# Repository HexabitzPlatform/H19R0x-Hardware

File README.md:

# H19R0x-Hardware
Hexabitz 38 V/10A Sensored BLDC Module Hardware Design

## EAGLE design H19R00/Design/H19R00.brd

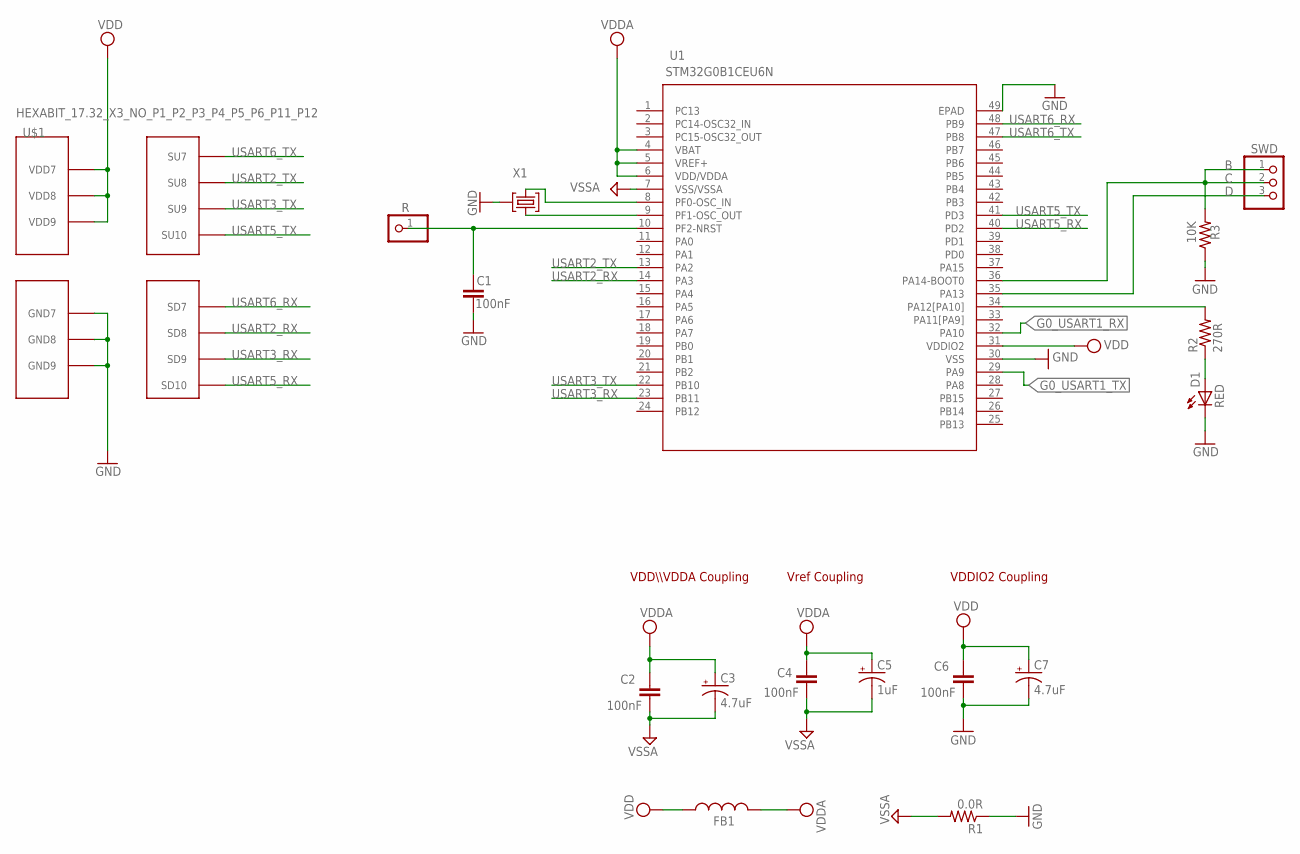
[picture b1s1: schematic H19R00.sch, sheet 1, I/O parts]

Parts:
C1: 100nF; C-0603; TOLERANCE 10%; VOLTAGE_RATING 16.0 V; MPN 0603YC104K4T2A
C2, C4, C6: 100nF; C-0603; TOLERANCE 10%; VOLTAGE_RATING 16.0 V; MPN '0603YC104K4T2A
C3: 4.7uF; C-0805-POL; TOLERANCE 20%; VOLTAGE_RATING 10.0 V; MPN '10TPU4R7MSI
C5: 1uF; C-0805-POL; TOLERANCE 20%; VOLTAGE_RATING 10.0 V; MPN 'CC0805KKX7R7BB105
C7: 4.7uF; C-0805-POL; TOLERANCE 10%; VOLTAGE_RATING 16.0 V; MPN '10TPU4R7MSI
D1: RED; VLMS1300-GS08
FB1: FB-TDK_MMZ1608Y300B; MPN MMZ1608Y300BTA00
R: PINHD-1X1; 1X01
R1: 0.0R; R-0603; MPN RC0603JR-070RL
R2: 270R; R-0603; MPN 'ERJ-3GEYJ271V
R3: 10K; R-0603; MPN '060300J0103T5E
SWD: PINHD-1X3; 1X03
U1: STM32G0B1CEU6N; HEXABITZ_ICS_QFN_B1CEU6_STM-L
U$1: HEXABIT_17.32_X3_NO_P1_P2_P3_P4_P5_P6_P11_P12
X1: 8MHZ; XTALL_CSTCE8M00G52; MPN CSTNE8M00G550000R0

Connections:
C: R3.2, SWD.1, SWD.2, U1.36 (PA14-BOOT0)
D: SWD.3, U1.35 (PA13)
G0_USART1_RX: U1.32 (PA10); also elsewhere on the board
G0_USART1_TX: U1.29 (PA9); also elsewhere on the board
GND: C1.1, C6.1, C7.2 (-), D1.C, R1.1, R3.1, U1.30 (VSS), U1.49 (EPAD), U$1.PAD_PD12 (GND7), U$1.PAD_PD17 (GND8), U$1.PAD_PD19 (GND9), X1.P$2 (2)
GND1: C2.1, C3.2 (-), C4.1, C5.2 (-), R1.2, U1.7 (VSS/VSSA); also elsewhere on the board
unnamed: U1.8 (PF0-OSC_IN), X1.P$1 (1)
unnamed: U1.9 (PF1-OSC_OUT), X1.P$3 (3)
unnamed: R2.2, U1.34 (PA12[PA10])
unnamed: D1.A, R2.1
unnamed: C1.2, R.1, U1.10 (PF2-NRST)
USART2_RX: U1.14 (PA3), U$1.PAD_PD1 (SD8)
USART2_TX: U1.13 (PA2), U$1.PAD_PU1 (SU8)
USART3_RX: U1.23 (PB11), U$1.PAD_PD2 (SD9)
USART3_TX: U1.22 (PB10), U$1.PAD_PU2 (SU9)
USART5_RX: U1.40 (PD2), U$1.PAD_PD8 (SD10)
USART5_TX: U1.41 (PD3), U$1.PAD_PU8 (SU10)
USART6_RX: U1.48 (PB9), U$1.PAD_PD3 (SD7)
USART6_TX: U1.47 (PB8), U$1.PAD_PU3 (SU7)
VDD: C6.2, C7.1 (+), FB1.1, U1.31 (VDDIO2), U$1.PAD_PU12 (VDD7), U$1.PAD_PU17 (VDD8), U$1.PAD_PU19 (VDD9); also elsewhere on the board
VDDA: C2.2, C3.1 (+), C4.2, C5.1 (+), FB1.2, U1.4 (VBAT), U1.5 (VREF+), U1.6 (VDD/VDDA)

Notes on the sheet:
VDDIO2 Coupling
VDD\\\VDDA Coupling
Vref Coupling

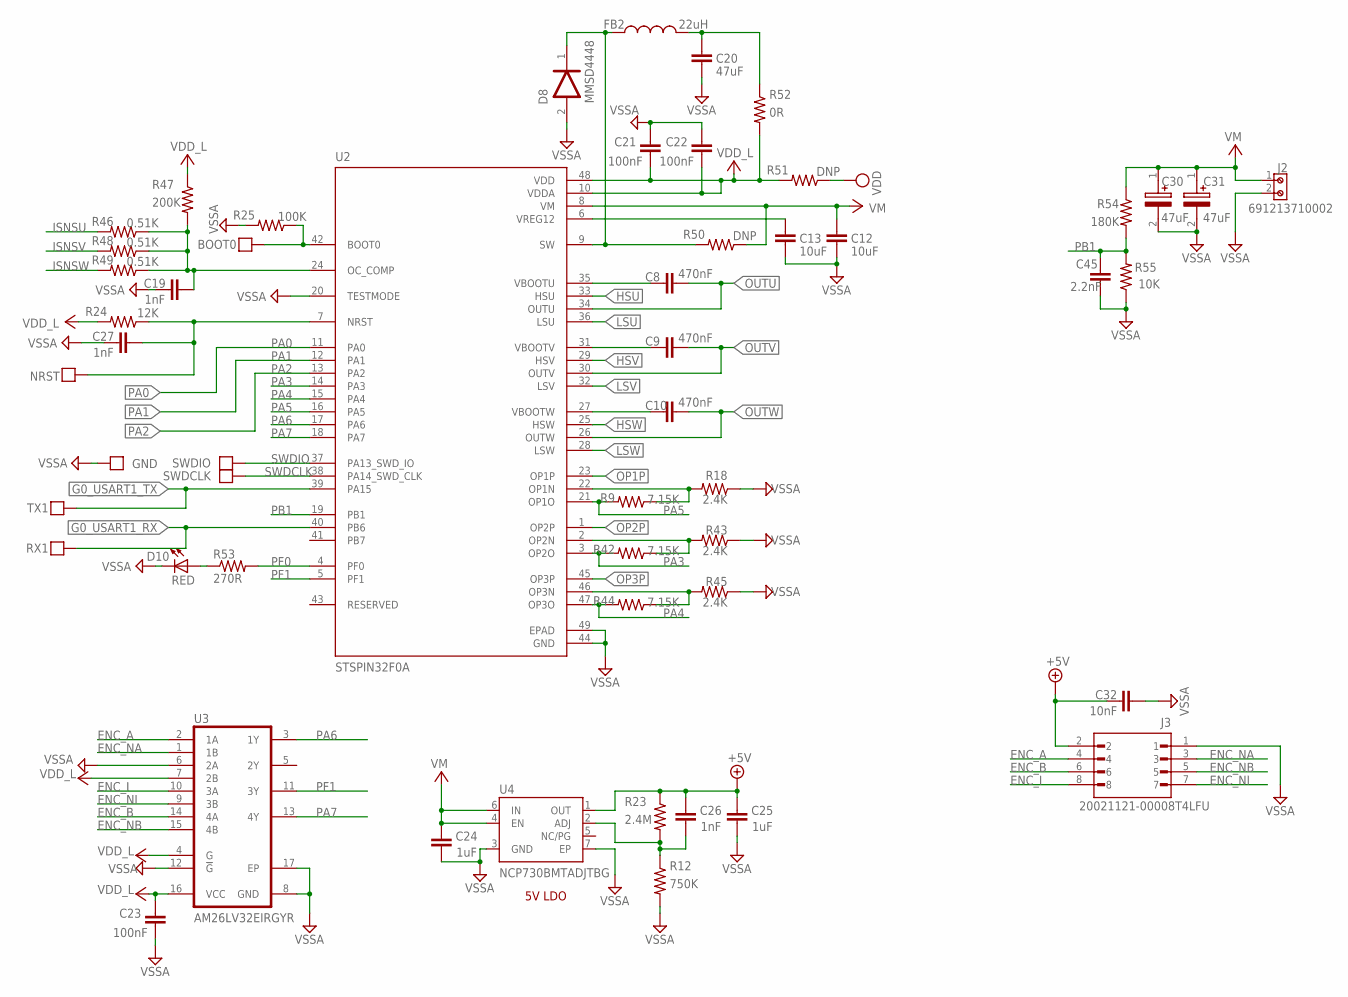
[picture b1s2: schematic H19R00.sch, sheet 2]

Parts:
BOOT0: PAD4
C8, C9, C10: 470nF; C-0603; TOLERANCE 10%; VOLTAGE_RATING 50V; MPN C1608X5R1H474K080AB
C12, C13: 10uF; C-0805; TOLERANCE 10%; VOLTAGE_RATING 50V; MPN GRM21BR61H106KE43K
C19, C26, C27: 1nF; C-0603; TOLERANCE 10%; VOLTAGE_RATING 50V; MPN CC0603KRNPO9BN102
C20: 47uF; C-0805; TOLERANCE 20%; VOLTAGE_RATING 10V; MPN GRM21BR61A476ME15K
C21, C22, C23: 100nF; C-0603; TOLERANCE 10%; VOLTAGE_RATING 16.0 V; MPN '0603YC104K4T2A
C24, C25: 1uF; C-0603; TOLERANCE 10%; VOLTAGE_RATING 50V; MPN UMK107BJ105KA-T
C30, C31: 47uF; CAPPRD350W60D825H1300
C32: 10nF; C-0603; TOLERANCE 10%; VOLTAGE_RATING 100V; MPN C0603X103K1RAC3316
C45: 2.2nF; C-0603; TOLERANCE 10%; VOLTAGE_RATING 16V; MPN C0603C222K4RECAUTO
D8: MMSD4448ONSEMI_MMSD4448_0_0; ONSEMI_MMSD4448_0
D10: RED; VLMS1300-GS08
FB2: 22uH; FB-0805; MPN MLZ2012P220WT000
GND: PAD4
J2: 691213710002
J3: 20021121-00008T4LFU; AMPHENOL_20021121-00008T4LF
NRST: PAD4
R9, R42, R44: 7.15K; R-0603; TOLERANCE 1%; MPN RC0603FR-0710K5L
R12: 750K; R-0603; TOLERANCE 1%; MPN RC0603FR-07750KL
R18, R43, R45: 2.4K; R-0603; TOLERANCE 1%; MPN RC0603FR-132K4L
R23: 2.4M; R-0603; TOLERANCE 1%; MPN RC0603FR-072M4L
R24: 12K; R-0603; TOLERANCE 1%; MPN RC0603FR-0712KL
R25: 100K; R-0603; TOLERANCE 1%; MPN RC0603FR-07100KL
R46, R48, R49: 0.51K; R-0603; TOLERANCE 1%; MPN RC0603FR-102K2L
R47: 200K; R-0603; TOLERANCE 1%; MPN RC0603FR-0718KL
R50, R51: DNP; R-0603; MPN DNP
R52: 0R; R-0603; TOLERANCE 1%; MPN RC0603FR-070RL
R53: 270R; R-0603; MPN 'ERJ-3GEYJ271V
R54: 180K; R-0603; TOLERANCE 1%; MPN RC0603FR-07180KL
R55: 10K; R-0603; MPN '060300J0103T5E
RX1: PAD4
SWDCLK: PAD4
SWDIO: PAD4
TX1: PAD4
U2: STSPIN32F0A; IC_STSPIN32F0A
U3: AM26LV32EIRGYRTEXAS_INSTRUMENTS_AM26LV32EIRGYR_0_0; TEXAS_INSTRUMENTS_AM26LV32EIRGYR_0
U4: NCP730BMTADJTBGON_SEMI_NCP730BMTADJTBG_0_0; ON_SEMI_NCP730BMTADJTBG_0

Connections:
+5V: C25.2, C26.2, C32.1, J3.2, R23.1, U4.1 (OUT); also elsewhere on the board
ENC_A: J3.4, U3.2 (1A)
ENC_B: J3.6, U3.14 (4A)
ENC_I: J3.8, U3.10 (3A)
ENC_NA: J3.3, U3.1 (1B)
ENC_NB: J3.5, U3.15 (4B)
ENC_NI: J3.7, U3.9 (3B)
G0_USART1_RX: RX1.P$1, U2.40 (PB6); also elsewhere on the board
G0_USART1_TX: TX1.P$1, U2.39 (PA15); also elsewhere on the board
GND1: C12.2, C13.2, C19.1, C20.2, C21.2, C22.2, C23.1, C24.1, C25.1, C27.1, C30.2 (-), C31.2 (-), C32.2, C45.1, D8.2 (ANODE), D10.C, GND.P$1, J2.2, J3.1, R12.2, R18.1, R25.2, R43.1, R45.1, R55.1, U2.20 (TESTMODE), U2.44 (GND), U2.49 (EPAD), U3.8 (GND), U3.12 (!G!), U3.17 (EP), U4.3 (GND), U4.7 (EP); also elsewhere on the board
HSU: U2.33 (HSU); also elsewhere on the board
HSV: U2.29 (HSV); also elsewhere on the board
HSW: U2.25 (HSW); also elsewhere on the board
ISNSU: R46.2; also elsewhere on the board
ISNSV: R48.2; also elsewhere on the board
ISNSW: R49.2; also elsewhere on the board
LSU: U2.36 (LSU); also elsewhere on the board
LSV: U2.32 (LSV); also elsewhere on the board
LSW: U2.28 (LSW); also elsewhere on the board
unnamed: R42.1, R43.2, U2.2 (OP2N)
unnamed: C8.2, U2.35 (VBOOTU)
unnamed: C9.2, U2.31 (VBOOTV)
unnamed: C10.2, U2.27 (VBOOTW)
unnamed: C26.1, R12.1, R23.2, U4.2 (ADJ)
unnamed: C27.2, NRST.P$1, R24.1, U2.7 (NRST)
unnamed: C13.1, U2.6 (VREG12)
unnamed: BOOT0.P$1, R25.1, U2.42 (BOOT0)
unnamed: R9.1, R18.2, U2.22 (OP1N)
unnamed: R44.1, R45.2, U2.46 (OP3N)
unnamed: C19.2, R46.1, R47.2, R48.1, R49.1, U2.24 (OC_COMP)
unnamed: D10.A, R53.1
unnamed: D8.1 (CATHODE), FB2.1, R50.2, U2.9 (SW)
unnamed: C20.1, FB2.2, R52.1
OP1P: U2.23 (OP1P); also elsewhere on the board
OP2P: U2.1 (OP2P); also elsewhere on the board
OP3P: U2.45 (OP3P); also elsewhere on the board
OUTU: C8.1, U2.34 (OUTU); also elsewhere on the board
OUTV: C9.1, U2.30 (OUTV); also elsewhere on the board
OUTW: C10.1, U2.26 (OUTW); also elsewhere on the board
PA0: U2.11 (PA0); also elsewhere on the board
PA1: U2.12 (PA1); also elsewhere on the board
PA2: U2.13 (PA2); also elsewhere on the board
PA3: R42.2, U2.3 (OP2O), U2.14 (PA3)
PA4: R44.2, U2.15 (PA4), U2.47 (OP3O)
PA5: R9.2, U2.16 (PA5), U2.21 (OP1O)
PA6: U2.17 (PA6), U3.3 (1Y)
PA7: U2.18 (PA7), U3.13 (4Y)
PB1: C45.2, R54.2, R55.2, U2.19 (PB1)
PF0: R53.2, U2.4 (PF0)
PF1: U2.5 (PF1), U3.11 (3Y)
SWDCLK: SWDCLK.P$1, U2.38 (PA14_SWD_CLK)
SWDIO: SWDIO.P$1, U2.37 (PA13_SWD_IO)
VDD: R51.1; also elsewhere on the board
VDD_L: C21.1, C22.1, C23.2, R24.2, R47.1, R51.2, R52.2, U2.10 (VDDA), U2.48 (VDD), U3.4 (G), U3.7 (2B), U3.16 (VCC); also elsewhere on the board
VM: C12.1, C24.2, C30.1 (+), C31.1 (+), J2.1, R50.1, R54.1, U2.8 (VM), U4.4 (EN), U4.6 (IN); also elsewhere on the board

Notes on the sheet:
5V LDO

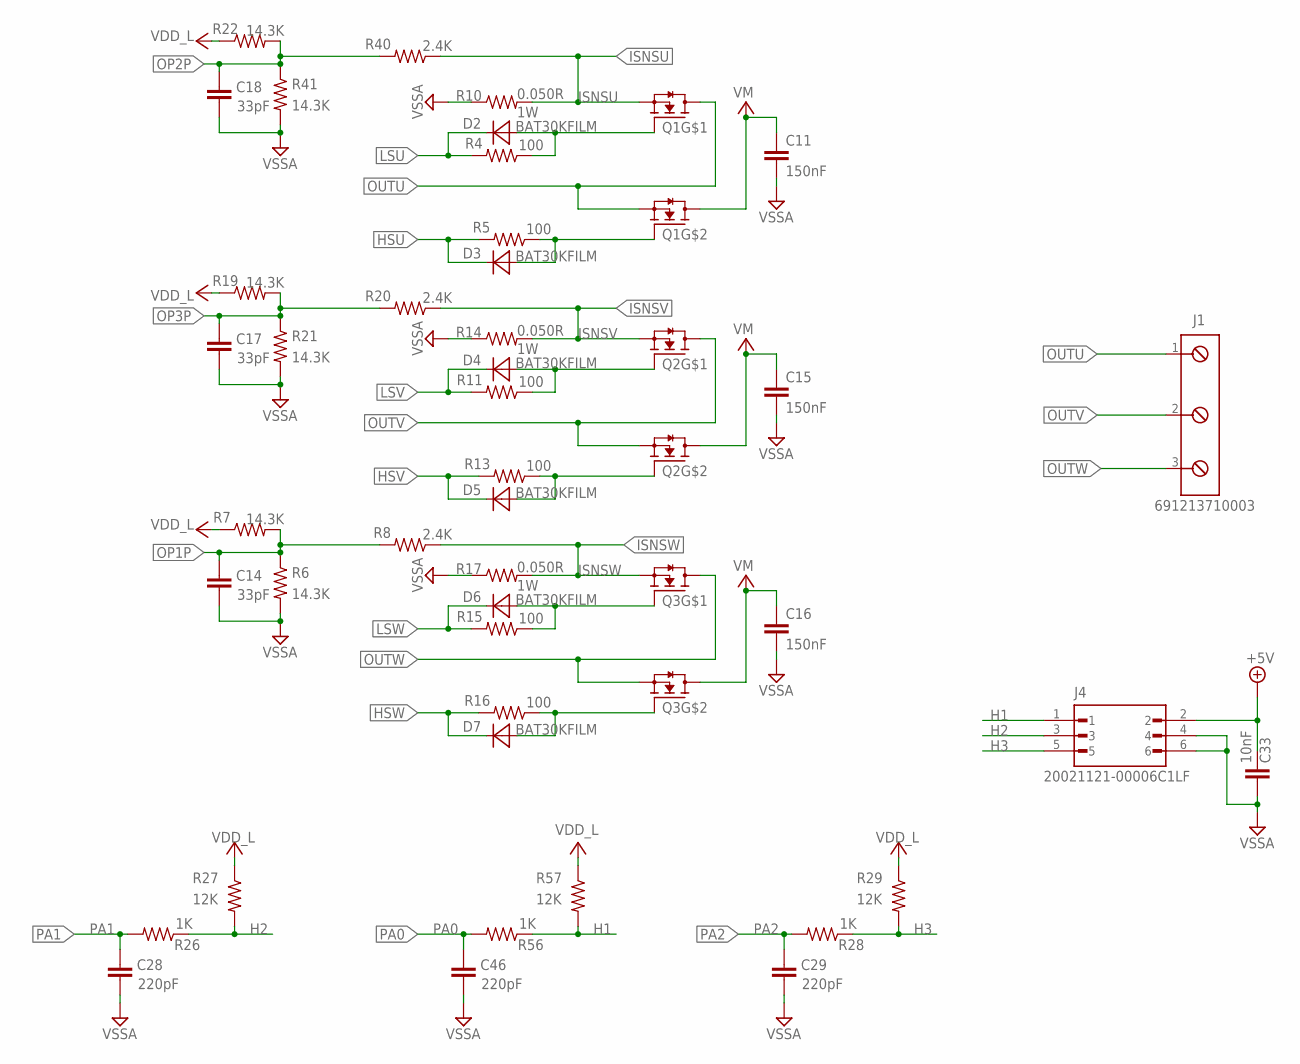
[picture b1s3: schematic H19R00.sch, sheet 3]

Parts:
C11, C15, C16: 150nF; C-0805; TOLERANCE 10%; VOLTAGE_RATING 100V; MPN C0805C154K1REC7800
C14, C17, C18: 33pF; C-0603; TOLERANCE 10%; VOLTAGE_RATING 50V; MPN 0603N330J500CT
C28, C29, C46: 220pF; C-0603; TOLERANCE 10%; VOLTAGE_RATING 50V; MPN 0603B221K500CT
C33: 10nF; C-0603; TOLERANCE 10%; VOLTAGE_RATING 100V; MPN C0603X103K1RAC3316
D2, D3, D4, D5, D6, D7: BAT30KFILM; STMICROELECTRONICS_BAT30KFILM_0
J1: 691213710003
J4: 20021121-00006C1LF; AMPHENOL_20021121-00006C1LF
Q1, Q2, Q3: PJQ5866A_R2_00001; PJQ5866A_R2_00001-8-POWERTDFN
R4, R5, R11, R13, R15, R16: 100; R-0603; TOLERANCE 1%; MPN AC0603FR-13100RL
R6, R7, R19, R21, R22, R41: 14.3K; R-0603; TOLERANCE 1%; MPN RC0603FR-0721KL
R8, R20, R40: 2.4K; R-0603; TOLERANCE 1%; MPN RC0603FR-132K4L
R10, R14, R17: 0.050R; R1206; TOLERANCE 1%; MPN ERJ-8BWFR100V
R26, R28, R56: 1K; R-0603; TOLERANCE 1%; MPN AC0603FR-131KL
R27, R29, R57: 12K; R-0603; TOLERANCE 1%; MPN RC0603FR-0712KL

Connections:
+5V: C33.1, J4.2; also elsewhere on the board
GND1: C11.2, C14.1, C15.2, C16.2, C17.1, C18.1, C28.1, C29.1, C33.2, C46.1, J4.4, J4.6, R6.2, R10.1, R14.1, R17.1, R21.2, R41.2; also elsewhere on the board
H1: J4.1, R56.1, R57.2
H2: J4.3, R26.1, R27.2
H3: J4.5, R28.1, R29.2
HSU: D3.C, R5.2; also elsewhere on the board
HSV: D5.C, R13.2; also elsewhere on the board
HSW: D7.C, R16.2; also elsewhere on the board
ISNSU: Q1.1 (S1), R10.2, R40.1; also elsewhere on the board
ISNSV: Q2.1 (S1), R14.2, R20.1; also elsewhere on the board
ISNSW: Q3.1 (S1), R8.1, R17.2; also elsewhere on the board
LSU: D2.C, R4.2; also elsewhere on the board
LSV: D4.C, R11.2; also elsewhere on the board
LSW: D6.C, R15.2; also elsewhere on the board
unnamed: D2.A, Q1.2 (G1), R4.1
unnamed: D4.A, Q2.2 (G1), R11.1
unnamed: D3.A, Q1.4 (G2), R5.1
unnamed: D5.A, Q2.4 (G2), R13.1
unnamed: D6.A, Q3.2 (G1), R15.1
unnamed: D7.A, Q3.4 (G2), R16.1
OP1P: C14.2, R6.1, R7.2, R8.2; also elsewhere on the board
OP2P: C18.2, R22.2, R40.2, R41.1; also elsewhere on the board
OP3P: C17.2, R19.2, R20.2, R21.1; also elsewhere on the board
OUTU: J1.1, Q1.3 (S2), Q1.7_8 (D1); also elsewhere on the board
OUTV: J1.2, Q2.3 (S2), Q2.7_8 (D1); also elsewhere on the board
OUTW: J1.3, Q3.3 (S2), Q3.7_8 (D1); also elsewhere on the board
PA0: C46.2, R56.2; also elsewhere on the board
PA1: C28.2, R26.2; also elsewhere on the board
PA2: C29.2, R28.2; also elsewhere on the board
VDD_L: R7.1, R19.1, R22.1, R27.1, R29.1, R57.1; also elsewhere on the board
VM: C11.1, C15.1, C16.1, Q1.5_6 (D2), Q2.5_6 (D2), Q3.5_6 (D2); also elsewhere on the board

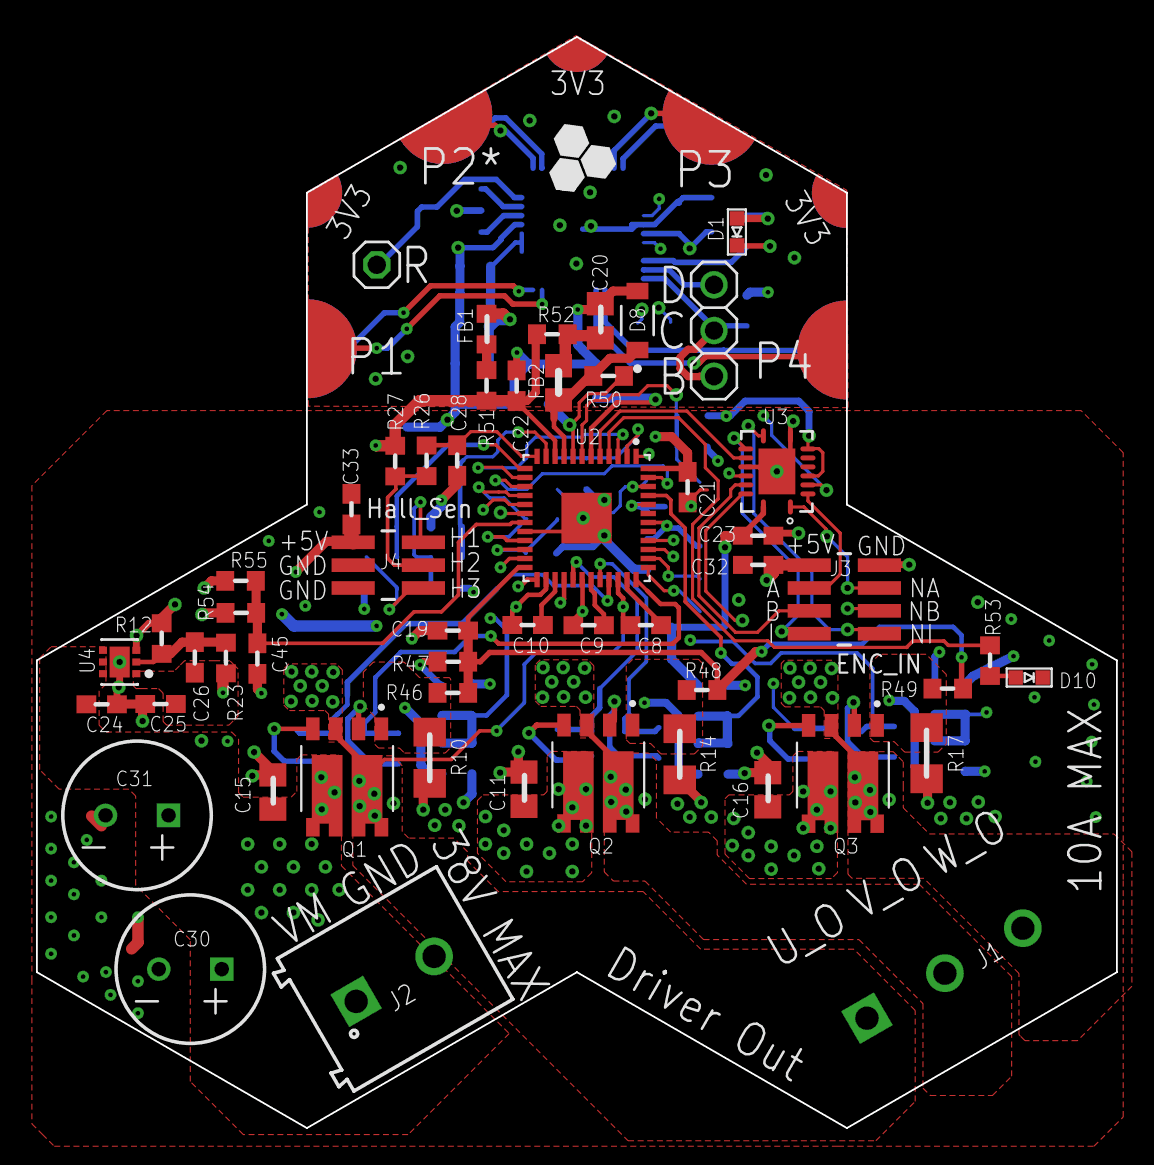
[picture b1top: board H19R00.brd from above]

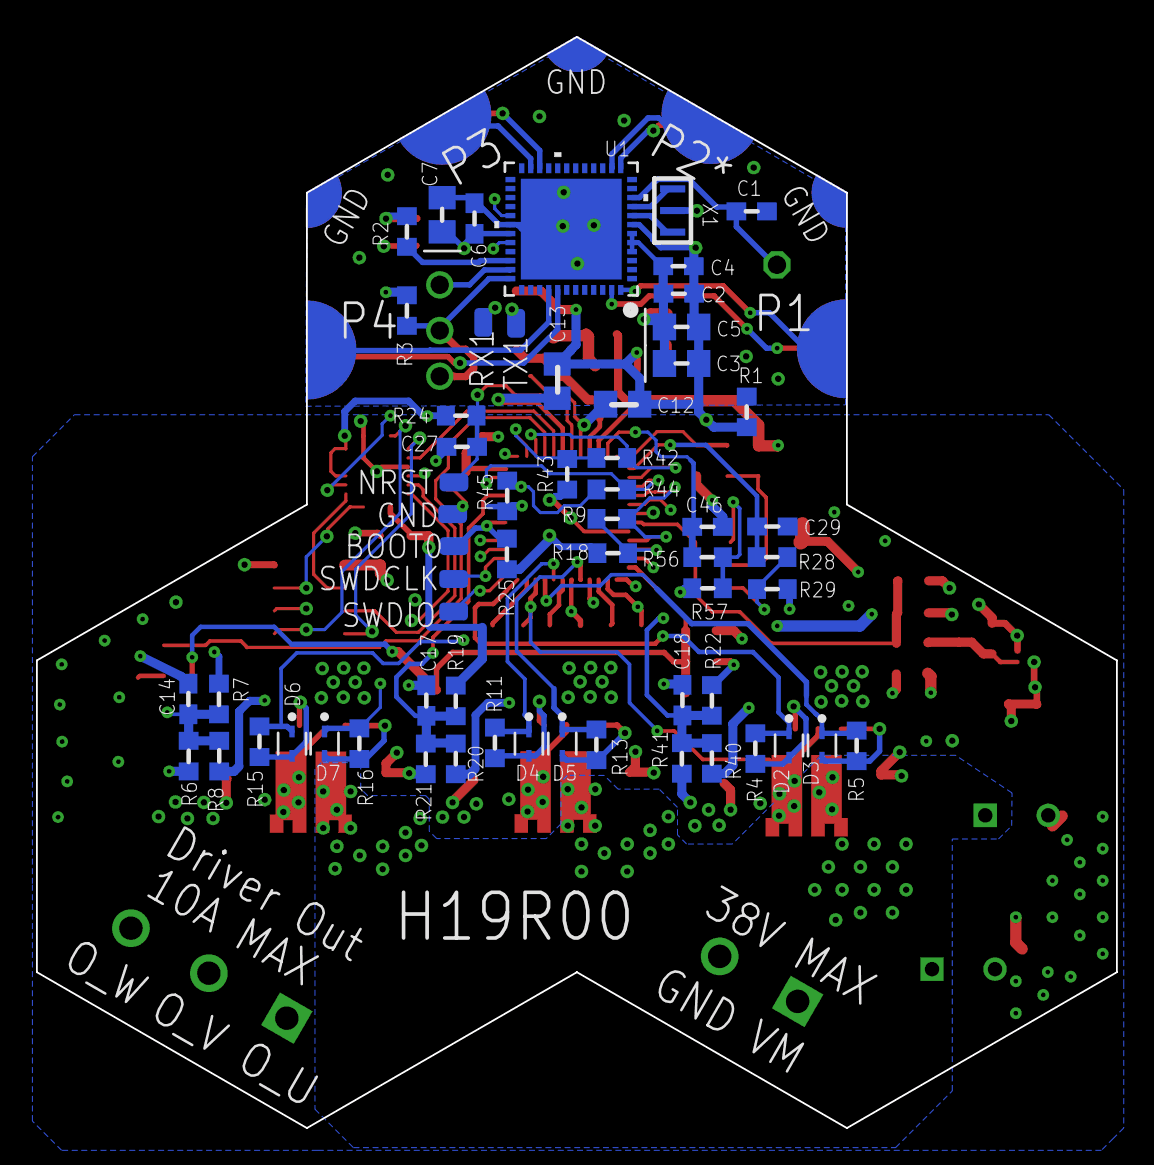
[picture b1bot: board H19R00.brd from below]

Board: 4 copper layers, 60.0 x 60.6 mm, 115 parts (60 on the bottom side), 81 nets.

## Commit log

2023-06-14 -Create the Back-end design
2023-06-15 -Add the logo and the module name to the layout
2023-10-10 -Adding the Original Files that has been designed by the Designer
2023-10-11 -Add some notes to the schematic -fix the BOM - Add NRST,TX1 and RX1 test points -Fix some issues at the silkscreen layer
2023-10-11 -Fix the BOM and some parts attributes
2023-10-12 -Fix the BOM
2023-11-05 -Before editing the layout
2023-11-10 All the edits that is related to 10A handling is done : -Improve the layout design so the pcb can handle continous current up to 10A -Naming the smd pin headers and thier pins on the silk screen laye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

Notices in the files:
parts and their libraries:
HEXABITZ_ICs: COPYRIGHT: Copyright (C) 2022 Ultra Librarian. All rights reserved.
